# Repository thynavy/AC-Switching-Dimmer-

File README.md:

# Project Title: **AC Switching (Dimmer)**

##  Introduction

This project presents an AC switching (dimmer) circuit designed to control the power delivered to an AC load, enabling adjustable brightness in lighting or variable speed in AC motors. The circuit is built with a 4N25 optocoupler, MOC3021 triac driver, and BTA16-600B triac, which together provide phase-controlled switching and electrical isolation. This setup allows for safe control of high-voltage AC loads through low-voltage control signals.

<p align="center">
    
    <br />
    <strong>Figure 1: The AC Switching (Dimmer) Module</strong>
</p>

##  Components Overview

1. **4N25 Optocoupler:** The 4N25 optocoupler electrically isolates the low-voltage control circuit from the high-voltage AC side, safeguarding sensitive components.
2. **MOC3021 Triac Driver:** The MOC3021 is an optoisolated triac driver that enables phase-angle control. By varying the phase angle of the AC signal, this component helps control power delivery to the load, achieving dimming functionality.
3. **BTA16-600B Triac:** The BTA16-600B triac is a high-power switching component that handles large AC currents. It is triggered by the MOC3021 and provides robust control for the AC load, such as lights or motors.

##  Design Documentation

###  Circuit Design

1. **Schematic Overview:** The schematic features the 4N25 optocoupler connected to the control circuit, ensuring isolation. The MOC3021 triac driver is then used to trigger the BTA16-600B triac in response to phase-angle control signals. This arrangement allows for precise control over the AC waveform delivered to the load.
  [Dimmer Schematic (PDF)](https://github.com/thynavy/AC_Switching_Dimmer/blob/main/Schematic.pdf)
3. **Phase Control Mechanism:**
   - The phase-angle control technique allows the circuit to adjust power by varying the point in the AC cycle where the triac is triggered. This approach modulates the average voltage delivered to the load.
   - The MOC3021 is triggered at different points in the AC cycle, controlling when the BTA16-600B triac conducts. The earlier the triac is triggered within each AC cycle, the higher the power delivered to the load.   
4. **Component Ratings:**   
   -  **4N25:** Rated for isolation up to 5kV, ensuring safe separation between control and AC load sides.
   - **MOC3021:** Designed to handle 400V, with adequate isolation for AC applications.
   - **BTA16-600B:** Rated for 16A and 600V, providing sufficient capacity for high-power AC loads.

###  PCB Layout

The PCB layout is designed to separate high-voltage and low-voltage sections, adhering to best practices for safety and electromagnetic compatibility (EMC). Key considerations include:
- **Isolation Zones:** Clear separation between the low-voltage control side (optocoupler and triac driver) and the high-voltage AC side (main triac and load).
- **Thermal Management:** Adequate spacing and thermal relief for the BTA16-600B triac to dissipate heat during operation.

###  Applications

This dimmer circuit can be used in various scenarios such as:
- **Lighting Control:** Adjusting brightness in AC lighting systems for energy savings and ambiance control.
- **Motor Speed Control:** Modulating speed in AC fan or motor applications.
- **Temperature Regulation:** Controlling heating elements by adjusting the power delivered to resistive loads.

##  Getting Started

###  Hardware Setup

1. **Connect the AC Load:** Attach the AC load (e.g., lamp or motor) to the output terminals of the BTA16-600B triac.
2. **Microcontroller Control:** Connect the low-voltage control circuit (e.g., Arduino or microcontroller) to the 4N25 optocoupler.
3. **Isolation and Grounding:**
   - Ensure that there is clear isolation between the low-voltage control circuit and the high-voltage AC components.
   - Verify grounding for safety and stability.

###  Software Control

1. **Phase Control Algorithm:** Write a control algorithm to vary the phase angle by triggering the 4N25 optocoupler at different points in the AC cycle.
2. **Adjusting Power Output:** Use pulse-width modulation (PWM) or a timer to adjust the triggering phase angle in each AC cycle to modulate the power delivered to the load.

##  Usage Guidelines

1. **Load Limitations:** Ensure that the load does not exceed the BTA16-600B triac’s maximum current rating (16A). Exceeding this may result in overheating or damage.
2. **Testing the Circuit:** Test the circuit with a lower voltage or a small resistive load before applying it to full AC mains power to verify functionality and safety.
3. **Monitoring Temperature:** Regularly monitor the temperature of the BTA16-600B triac. Consider using a heat sink if high power loads are used for prolonged periods.

## Safety Precautions

<span style="color:red"> _**Warning**:__**This circuit involves high-voltage AC power, which can be dangerous or fatal if mishandled. Follow these safety guidelines strictly.**_ </span>

1. Circuit Isolation:
   - Maintain strict separation between the low-voltage (control) side and high-voltage (AC load) side of the circuit. The 4N25 and MOC3021 are optoisolators that help ensure this isolation, but physical separation on the PCB is essential.
2. Protective Equipment:
   - Always wear protective equipment (e.g., insulated gloves, safety glasses) when working with high-voltage AC circuits.
3. Proper Enclosure:
   - Enclose the circuit in a non-conductive box to prevent accidental contact with high-voltage components.
4. Testing Precautions:
   - When testing, use an isolation transformer to reduce the risk of electrical shock and avoid working alone.
5. Heat Management:
   - High-power loads can cause the triac to generate substantial heat. Ensure adequate ventilation and consider adding a heat sink if necessary.
6. Emergency Preparedness:
   - Keep an accessible power cutoff switch nearby and make sure you know how to safely disconnect the circuit in an emergency.

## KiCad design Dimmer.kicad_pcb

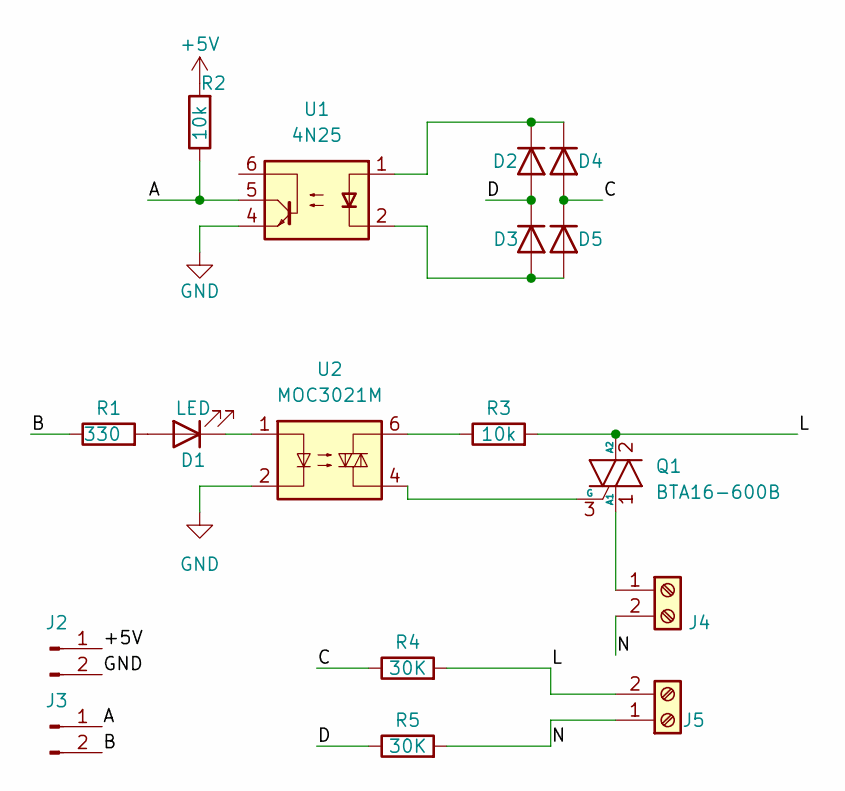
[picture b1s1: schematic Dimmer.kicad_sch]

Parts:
D1: LED; LED_D5.0mm
D2, D3, D4, D5: 1N4007; D_DO-41_SOD81_P10.16mm_Horizontal
J2, J3: Conn_01x02_Male; JST_XH_B2B-XH-A_1x02_P2.50mm_Vertical
J4, J5: Screw_Terminal_01x02; TerminalBlock_Phoenix_MKDS-1,5-2-5.08_1x02_P5.08mm_Horizont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
Q1: BTA16-600B; TO-220-3_Vertical
R1: 330; R_Axial_DIN0207_L6.3mm_D2.5mm_P7.62mm_Horizontal
R2, R3: 10k; R_Axial_DIN0207_L6.3mm_D2.5mm_P7.62mm_Horizontal
R4, R5: 30K; R_Axial_DIN0207_L6.3mm_D2.5mm_P7.62mm_Horizontal
U1: 4N25; DIP-6_W7.62mm_LongPads
U2: MOC3021M; DIP-6_W7.62mm_LongPads

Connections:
+5V: J2.1, R2.2
/A: J3.1, R2.1, U1.5
/B: J3.2, R1.1
/C: D4.2 (A), D5.1 (K), R4.1
/D: D2.2 (A), D3.1 (K), R5.1
/L: J5.2, Q1.2 (A2), R3.2, R4.2
/N: J4.2, J5.1, R5.2
GND: J2.2, U1.4, U2.2
unnamed: D1.1 (K), U2.1
unnamed: D1.2 (A), R1.2
unnamed: J4.1, Q1.1 (A1)
unnamed: Q1.3 (G), U2.4
unnamed: R3.1, U2.6
unnamed: D2.1 (K), D4.1 (K), U1.1
unnamed: D3.2 (A), D5.2 (A), U1.2

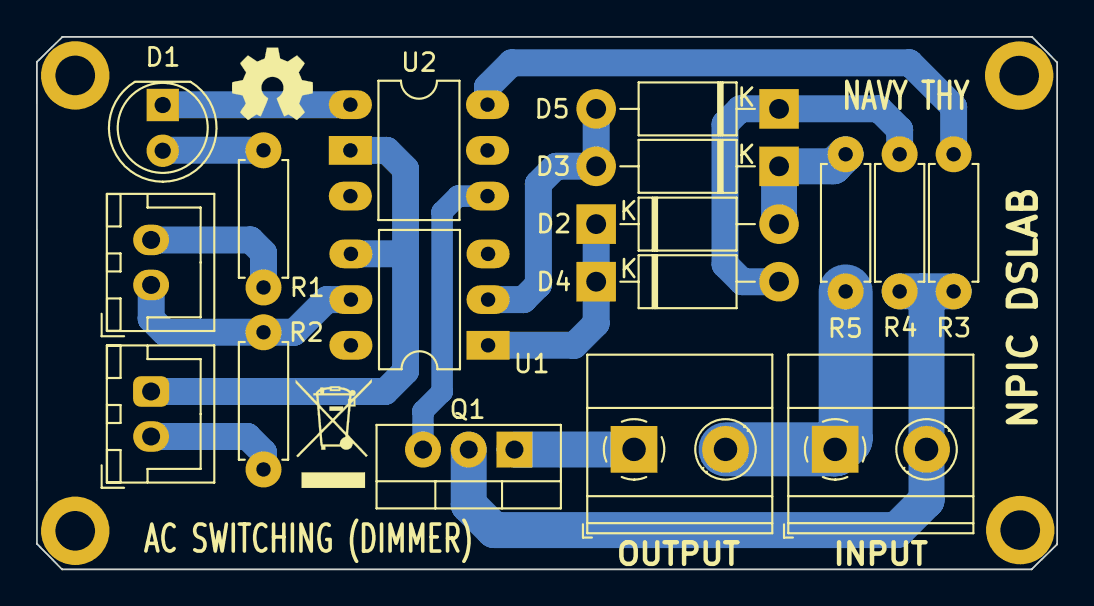
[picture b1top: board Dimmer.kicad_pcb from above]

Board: 2 copper layers, 56.7 x 29.6 mm, 17 parts (0 on the bottom side), 15 nets.
